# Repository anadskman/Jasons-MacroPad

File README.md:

# Jason's MacroPad

This is my first keyboard and I decided to make a small cut, copy, and paste board.
The board has 'Ctrl', 'X', 'C' and 'V'.
I added a Oled screen and a rotary encoder to display your pc's clipboard.

### My Experience

I had a fun time making this keyboard, its a different side of engineering I enjoy.
I faced a few difficulties, mainly just the firmware, while making this but thanks to Hackclubs guides I got by. 

### Parts

- 4x Cherry MX Switches
- 1x 0.91 inch OLED display
- 2x SK6812 MINI Leds
- 1x XIAO RP2040
- 4x Blank DSA Keycaps
- 4x M3x16 Bolt
- 4x M3 Heatset
- 1x EC11 Rotary encoder

- QMK Firmware
- send-clipboard.py
- Top Case.stl
- Bottom Case.stl

Schematic            |  PCB         |   Case
:-------------------------:|:-------------------------:|:-------------------------:|
 |  | 

## Finished Product

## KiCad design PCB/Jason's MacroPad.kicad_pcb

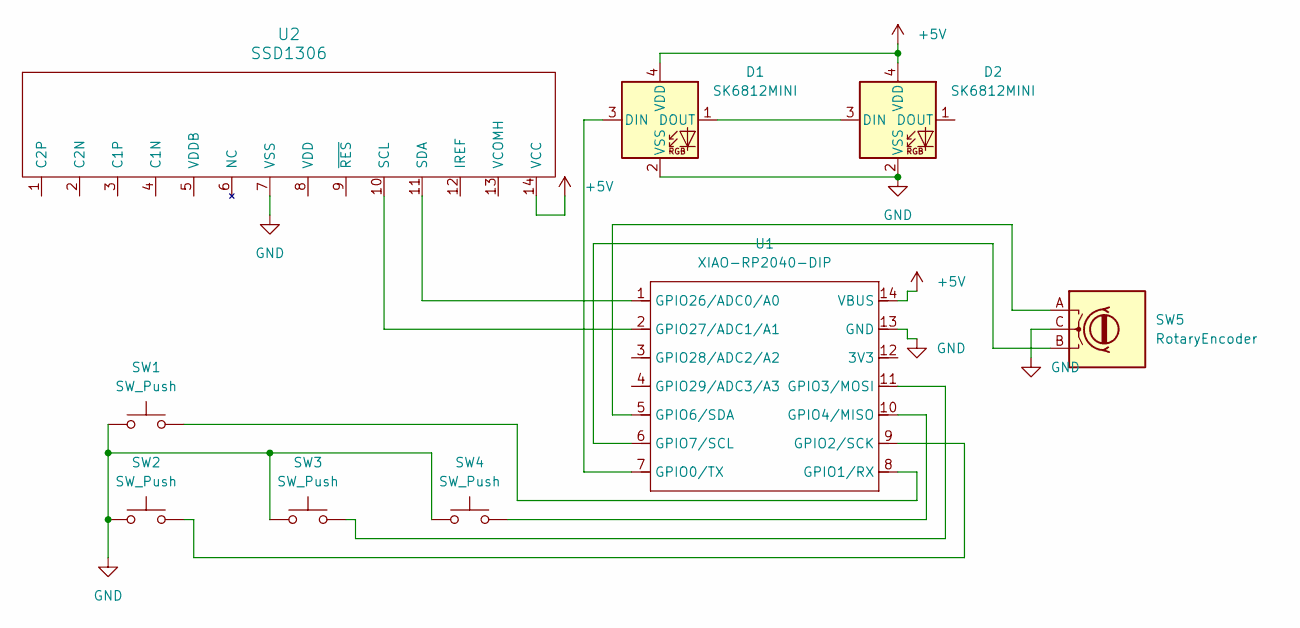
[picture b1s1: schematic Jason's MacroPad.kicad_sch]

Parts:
D1, D2: SK6812MINI; LED_SK6812MINI_PLCC4_3.5x3.5mm_P1.75mm
SW1, SW2, SW3, SW4: SW_Push; SW_Cherry_MX_1.00u_PCB
SW5: RotaryEncoder; RotaryEncoder_Alps_EC11E-Switch_Vertical_H20mm
U1: XIAO-RP2040-DIP
U2: SSD1306; SSD1306_OLED-0.91-128x32

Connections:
+5V: D1.4 (VDD), D2.4 (VDD), U1.14 (VBUS), U2.14 (VCC)
GND: D1.2 (VSS), D2.2 (VSS), SW1.1, SW2.1, SW3.1, SW4.1, SW5.C, U1.13 (GND), U2.7 (VSS)
unnamed: D1.3 (DIN), U1.7 (GPIO0/TX)
unnamed: D1.1 (DOUT), D2.3 (DIN)
unnamed: SW1.2, U1.8 (GPIO1/RX)
unnamed: SW2.2, U1.9 (GPIO2/SCK)
unnamed: SW3.2, U1.11 (GPIO3/MOSI)
unnamed: SW4.2, U1.10 (GPIO4/MISO)
unnamed: SW5.A, U1.5 (GPIO6/SDA)
unnamed: SW5.B, U1.6 (GPIO7/SCL)
unnamed: U1.1 (GPIO26/ADC0/A0), U2.11 (SDA)
unnamed: U1.2 (GPIO27/ADC1/A1), U2.10 (SCL)

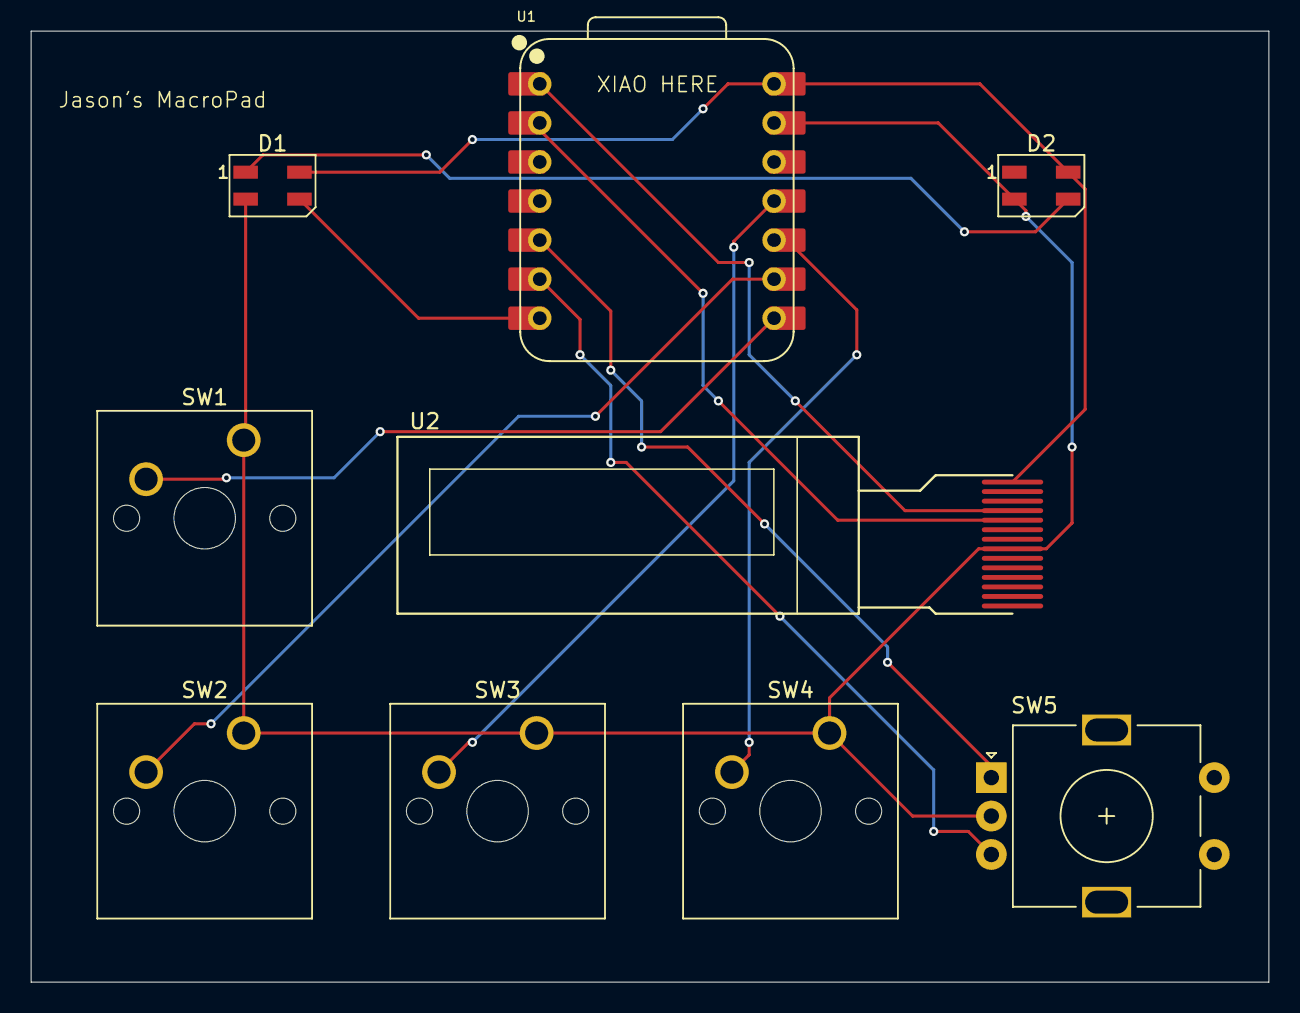
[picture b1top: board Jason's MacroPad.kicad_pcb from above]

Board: 2 copper layers, 80.5 x 61.8 mm, 9 parts (0 on the bottom side), 12 nets.

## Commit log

2025-12-28 Changed First Image to Unrendered Model in README.md
2025-12-28 Changed Cad File
2026-01-28 Change button pins
